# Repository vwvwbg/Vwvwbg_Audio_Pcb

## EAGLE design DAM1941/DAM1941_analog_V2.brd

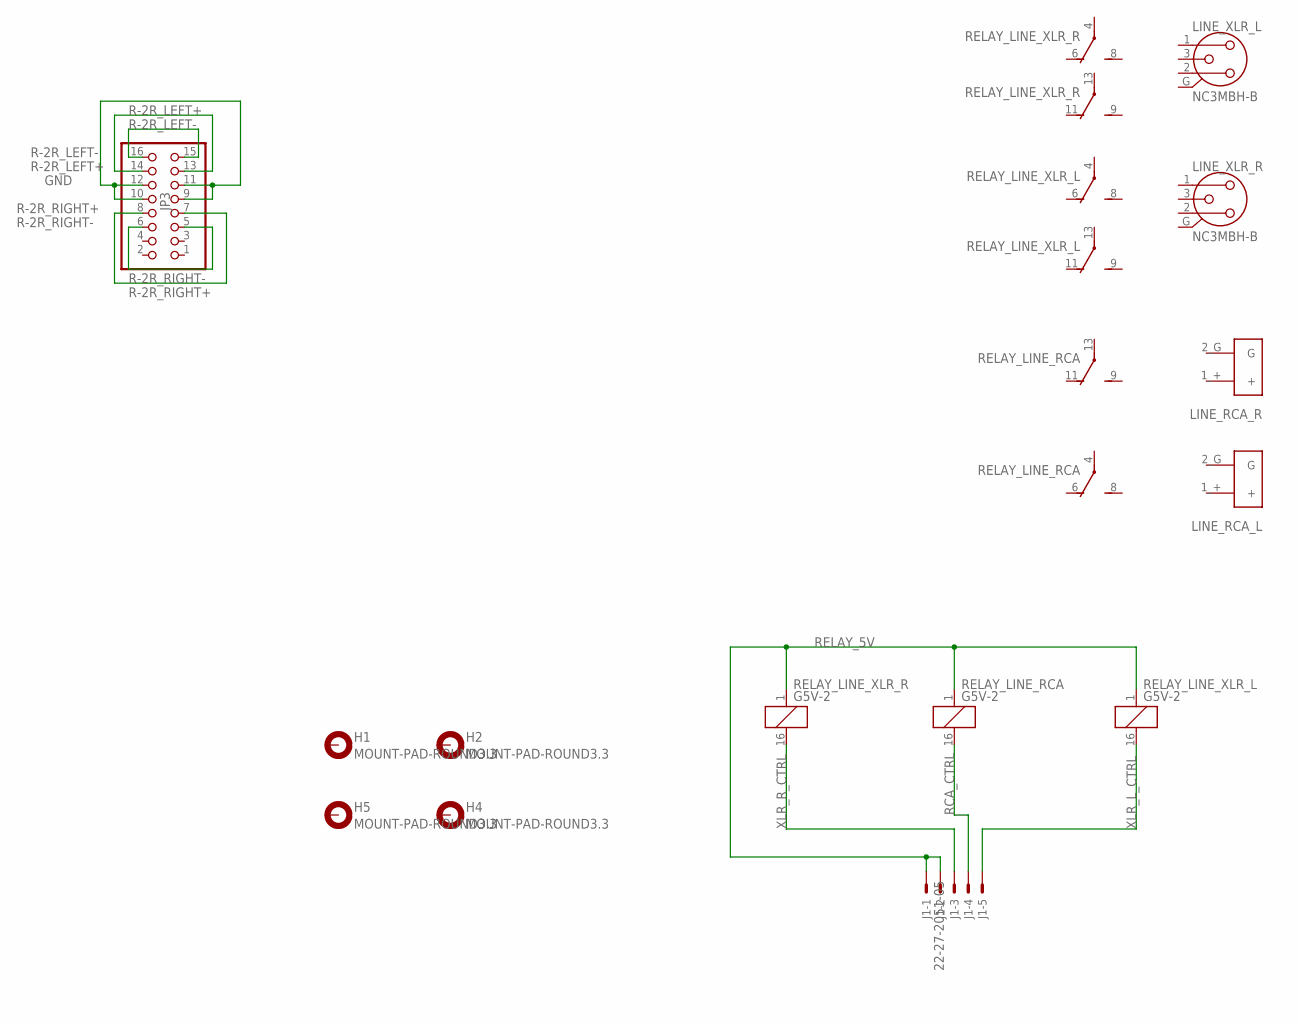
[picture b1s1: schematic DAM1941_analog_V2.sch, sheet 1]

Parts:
H1, H2, H4, H5: MOUNT-PAD-ROUND3.3; 3,3-PAD
J1: 22-27-2051-05; 6410-05
JP3: PINHD-2X8; 2X08
LINE_RCA_L: RCA
LINE_RCA_R: RCA
LINE_XLR_L: NC3MBH-B
LINE_XLR_R: NC3MBH-B
RELAY_LINE_RCA: G5V-2
RELAY_LINE_XLR_L: G5V-2
RELAY_LINE_XLR_R: G5V-2

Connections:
GND: JP3.9, JP3.10, JP3.11, JP3.12; also elsewhere on the board
R-2R_LEFT+: JP3.13, JP3.14
R-2R_LEFT-: JP3.15, JP3.16
R-2R_RIGHT+: JP3.7, JP3.8
R-2R_RIGHT-: JP3.5, JP3.6
RCA_CTRL: J1.4, RELAY_LINE_RCA.16 (2)
RELAY_5V: J1.1, J1.2, RELAY_LINE_RCA.1, RELAY_LINE_XLR_L.1, RELAY_LINE_XLR_R.1
XLR_L_CTRL: J1.5, RELAY_LINE_XLR_L.16 (2)
XLR_R_CTRL: J1.3, RELAY_LINE_XLR_R.16 (2)

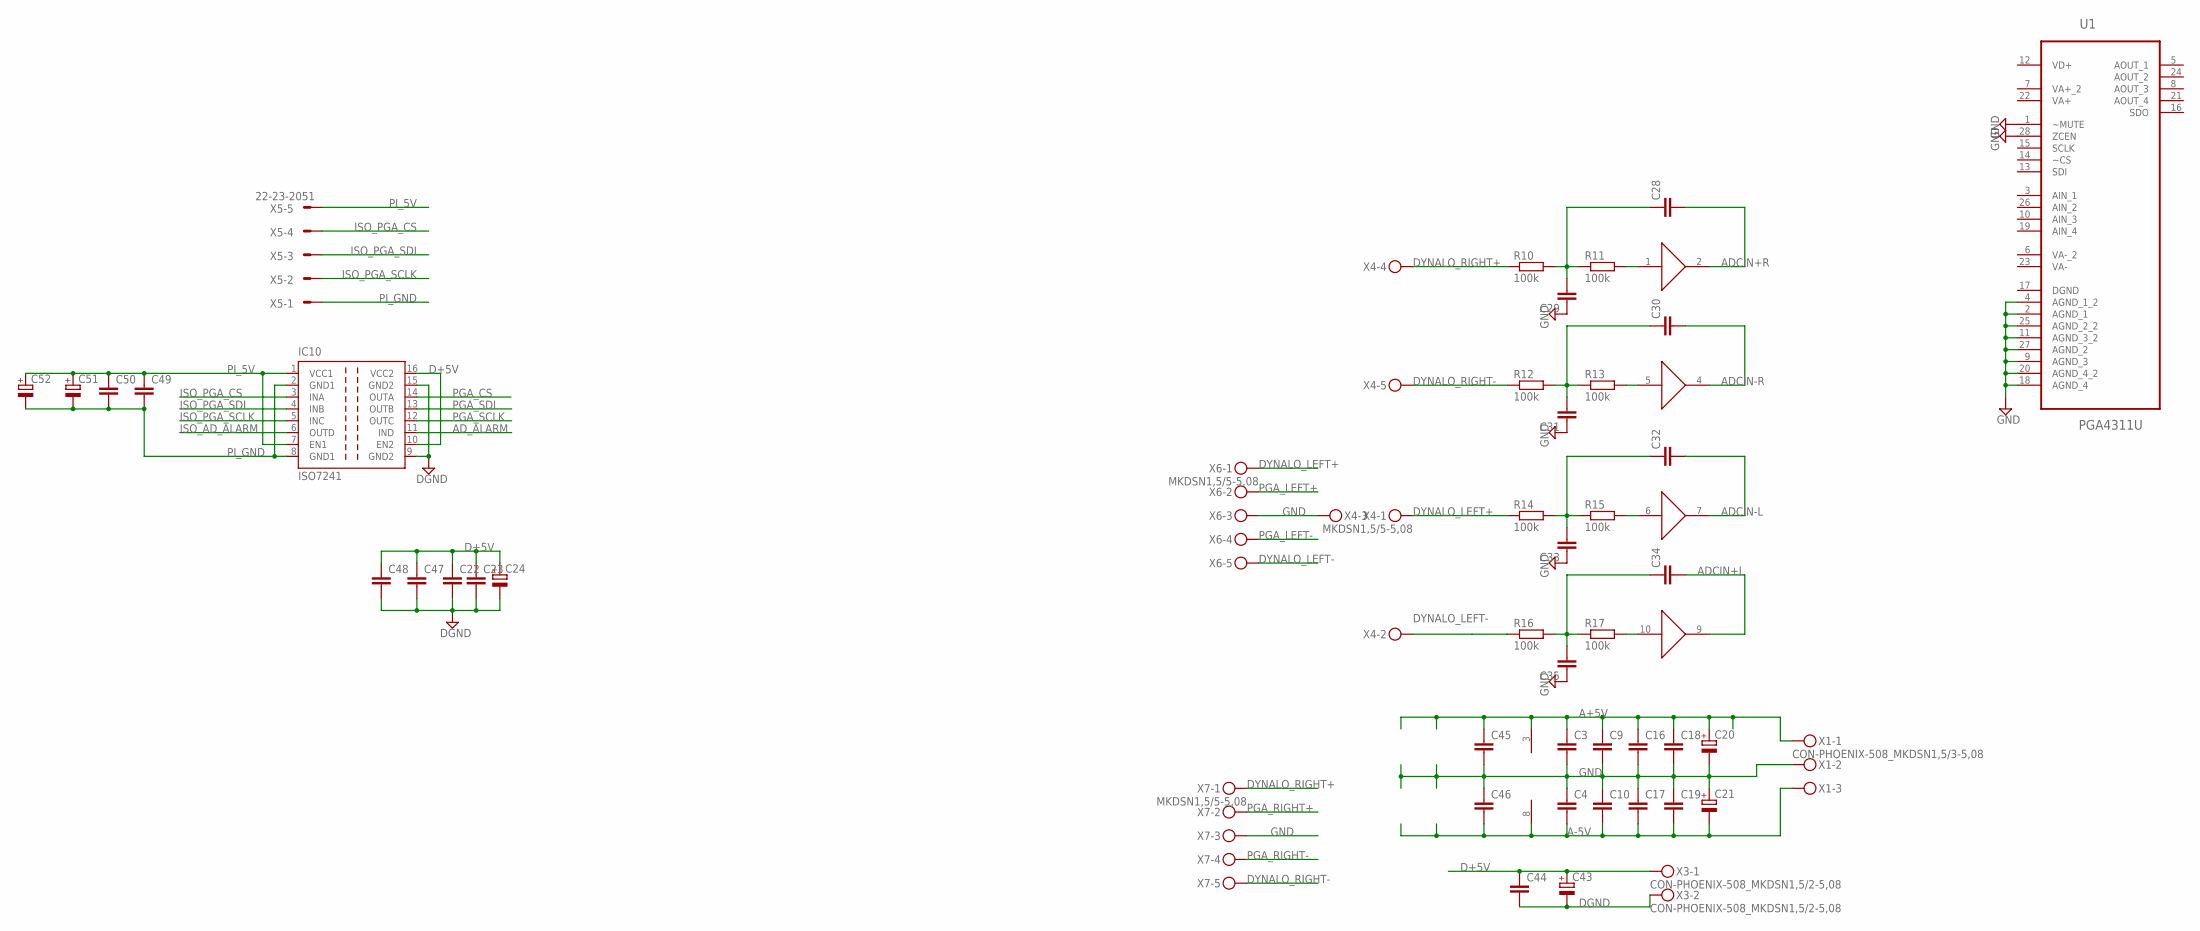
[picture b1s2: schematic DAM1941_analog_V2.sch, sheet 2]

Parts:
C3, C4, C9, C10, C16, C17, C18, C19, C22, C23, C44: C-EU050-050X075; C050-050X075
C20, C21, C24, C43: CPOL-EUE5-10.5; E5-10,5
C28, C29, C30, C31, C32, C33, C34, C35: C-EUC1206; C1206
C45, C46, C47, C48, C49, C50: C-EUC0603K; C0603K
C51, C52: CPOL-EUE5-8.5; E5-8,5
IC10: ISO7241; SO-16DW
R10, R11, R12, R13, R14, R15, R16, R17: 100k; MINI_MELF-0204R
U1: PGA4311U; SOIC127P1030X265-28N
U$3: AD8244; MSOP10
X1: CON-PHOENIX-508_MKDSN1,5/3-5,08
X3: CON-PHOENIX-508_MKDSN1,5/2-5,08
X4, X6, X7: MKDSN1,5/5-5,08
X5: 22-23-2051

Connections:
A+5V: C3.1, C9.1, C16.1, C18.1, C20.+, C45.1, U$3.3 (V+), X1.1; also elsewhere on the board
A-5V: C4.2, C10.2, C17.2, C19.2, C21.-, C46.2, U$3.8 (V-), X1.3
ADCIN+L: C34.2, U$3.9 (OUT); also elsewhere on the board
ADCIN+R: C28.2, U$3.2 (OUT); also elsewhere on the board
ADCIN-L: C32.2, U$3.7 (OUT); also elsewhere on the board
ADCIN-R: C30.2, U$3.4 (OUT); also elsewhere on the board
AD_ALARM: IC10.11 (IND); also elsewhere on the board
D+5V: C22.1, C23.1, C24.+, C43.+, C44.1, C47.1, C48.1, IC10.10 (EN2), IC10.16 (VCC2), X3.1; also elsewhere on the board
DGND: C22.2, C23.2, C24.-, C43.-, C44.2, C47.2, C48.2, IC10.9 (GND2), IC10.15 (GND2), X3.2; also elsewhere on the board
DYNALO_LEFT+: R14.1, X4.1, X6.1
DYNALO_LEFT-: R16.1, X4.2, X6.5
DYNALO_RIGHT+: R10.1, X4.4, X7.1
DYNALO_RIGHT-: R12.1, X4.5, X7.5
GND: C3.2, C4.1, C9.2, C10.1, C16.2, C17.1, C18.2, C19.1, C20.-, C21.+, C29.1, C31.1, C33.1, C35.1, C45.2, C46.1, U1.1 (~MUTE), U1.2 (AGND_1), U1.4 (AGND_1_2), U1.9 (AGND_3), U1.11 (AGND_3_2), U1.18 (AGND_4), U1.20 (AGND_4_2), U1.25 (AGND_2_2), U1.27 (AGND_2), U1.28 (ZCEN), X1.2, X4.3, X6.3, X7.3; also elsewhere on the board
ISO_AD_ALARM: IC10.6 (OUTD); also elsewhere on the board
ISO_PGA_CS: IC10.3 (INA), X5.4
ISO_PGA_SCLK: IC10.5 (INC), X5.2
ISO_PGA_SDI: IC10.4 (INB), X5.3
unnamed: C28.1, C29.2, R10.2, R11.1
unnamed: R11.2, U$3.1 (IN)
unnamed: C30.1, C31.2, R12.2, R13.1
unnamed: R13.2, U$3.5 (IN)
unnamed: C32.1, C33.2, R14.2, R15.1
unnamed: R15.2, U$3.6 (IN)
unnamed: C34.1, C35.2, R16.2, R17.1
unnamed: R17.2, U$3.10 (IN)
PGA_CS: IC10.14 (OUTA)
PGA_LEFT+: X6.2
PGA_LEFT-: X6.4
PGA_RIGHT+: X7.2
PGA_RIGHT-: X7.4
PGA_SCLK: IC10.12 (OUTC)
PGA_SDI: IC10.13 (OUTB)
PI_5V: C49.1, C50.1, C51.+, C52.+, IC10.1 (VCC1), IC10.7 (EN1), X5.5; also elsewhere on the board
PI_GND: C49.2, C50.2, C51.-, C52.-, IC10.2 (GND1), IC10.8 (GND1), X5.1; also elsewhere on the board
VA+: U1.22 (VA+)
VA+_2: U1.7 (VA+_2)
VA-: U1.23 (VA-)
VA-_2: U1.6 (VA-_2)
VD+: U1.12 (VD+)

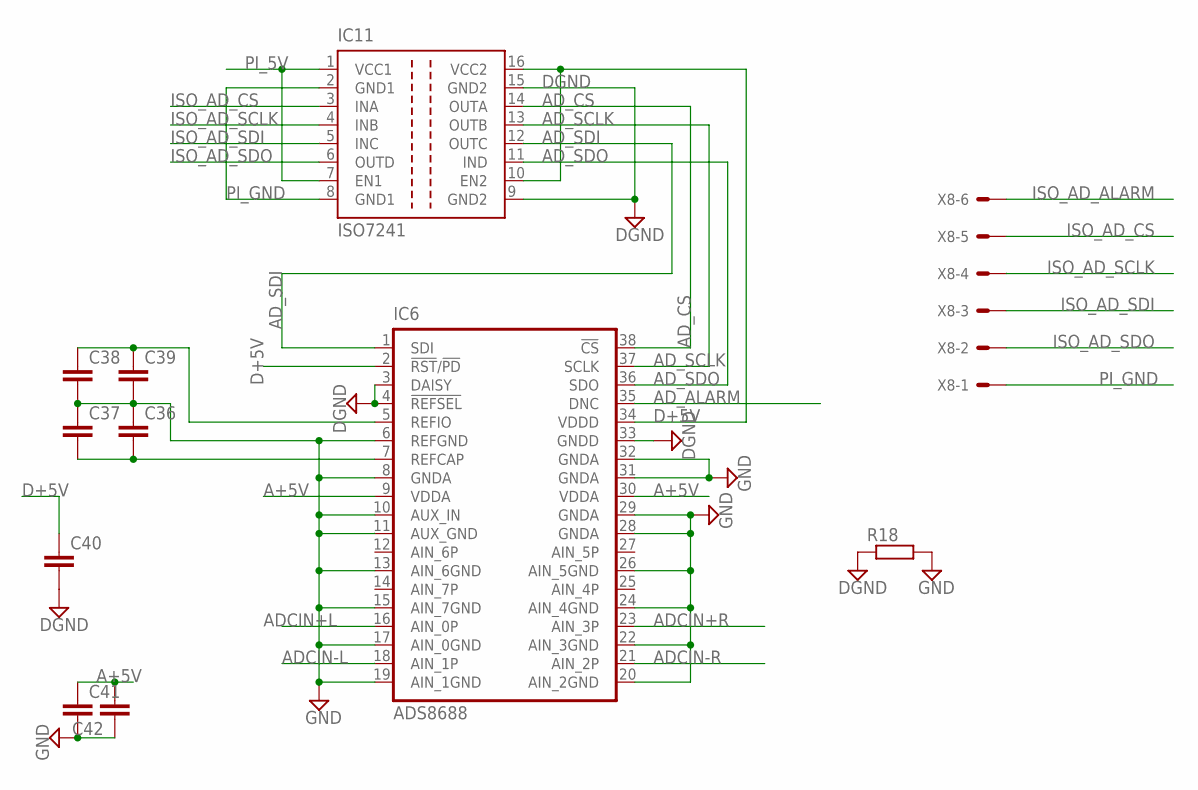
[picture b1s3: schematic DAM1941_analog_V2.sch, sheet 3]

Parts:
C36, C39, C40, C41, C42: C-EUC0603K; C0603K
C37, C38: C-EU050-035X075; C050-035X075
IC6: ADS8688; DBT_R-PDSO-G38
IC11: ISO7241; SO-16DW
R18: R-EU_MELF0204R; MINI_MELF-0204R
X8: 22-23-2061

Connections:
A+5V: C41.1, C42.2, IC6.9 (VDDA), IC6.30 (VDDA); also elsewhere on the board
ADCIN+L: IC6.16 (AIN_0P); also elsewhere on the board
ADCIN+R: IC6.23 (AIN_3P); also elsewhere on the board
ADCIN-L: IC6.18 (AIN_1P); also elsewhere on the board
ADCIN-R: IC6.21 (AIN_2P); also elsewhere on the board
AD_ALARM: IC6.35 (DNC); also elsewhere on the board
AD_CS: IC6.38 (!CS), IC11.14 (OUTA)
AD_SCLK: IC6.37 (SCLK), IC11.13 (OUTB)
AD_SDI: IC6.1 (SDI), IC11.12 (OUTC)
AD_SDO: IC6.36 (SDO), IC11.11 (IND)
D+5V: C40.1, IC6.2 (!RST!/!PD), IC6.34 (VDDD), IC11.10 (EN2), IC11.16 (VCC2); also elsewhere on the board
DGND: C40.2, IC6.3 (DAISY), IC6.4 (!REFSEL), IC6.33 (GNDD), IC11.9 (GND2), IC11.15 (GND2), R18.1; also elsewhere on the board
GND: C36.1, C37.1, C38.2, C39.2, C41.2, C42.1, IC6.6 (REFGND), IC6.8 (GNDA), IC6.10 (AUX_IN), IC6.11 (AUX_GND), IC6.13 (AIN_6GND), IC6.15 (AIN_7GND), IC6.17 (AIN_0GND), IC6.19 (AIN_1GND), IC6.20 (AIN_2GND), IC6.22 (AIN_3GND), IC6.24 (AIN_4GND), IC6.26 (AIN_5GND), IC6.28 (GNDA), IC6.29 (GNDA), IC6.31 (GNDA), IC6.32 (GNDA), R18.2; also elsewhere on the board
ISO_AD_ALARM: X8.6; also elsewhere on the board
ISO_AD_CS: IC11.3 (INA), X8.5
ISO_AD_SCLK: IC11.4 (INB), X8.4
ISO_AD_SDI: IC11.5 (INC), X8.3
ISO_AD_SDO: IC11.6 (OUTD), X8.2
unnamed: C36.2, C37.2, IC6.7 (REFCAP)
unnamed: C38.1, C39.1, IC6.5 (REFIO)
PI_5V: IC11.1 (VCC1), IC11.7 (EN1); also elsewhere on the board
PI_GND: IC11.2 (GND1), IC11.8 (GND1), X8.1; also elsewhere on the board

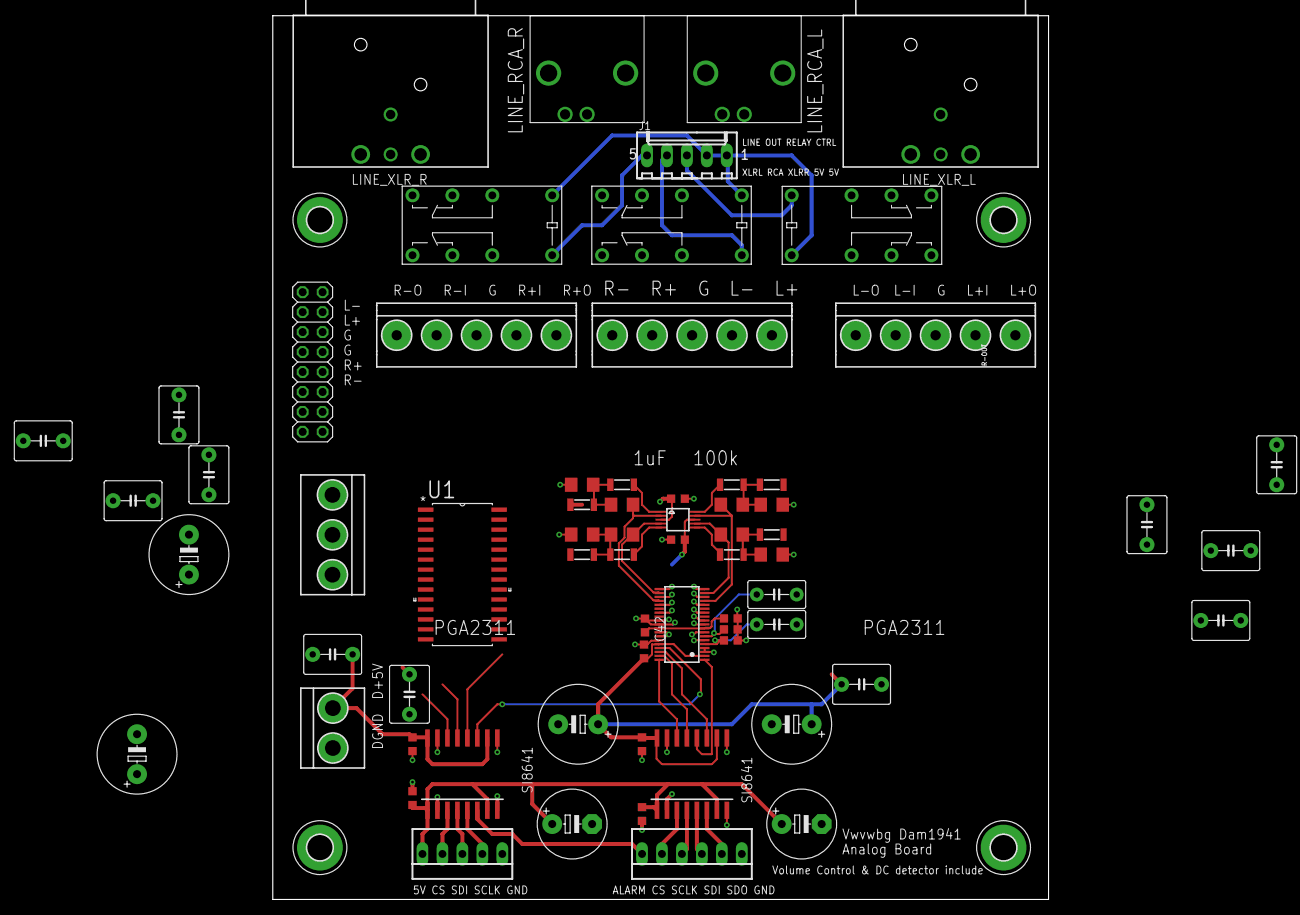
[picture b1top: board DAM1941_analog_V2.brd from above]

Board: 2 copper layers, 98.7 x 112.5 mm, 72 parts (1 on the bottom side), 46 nets.

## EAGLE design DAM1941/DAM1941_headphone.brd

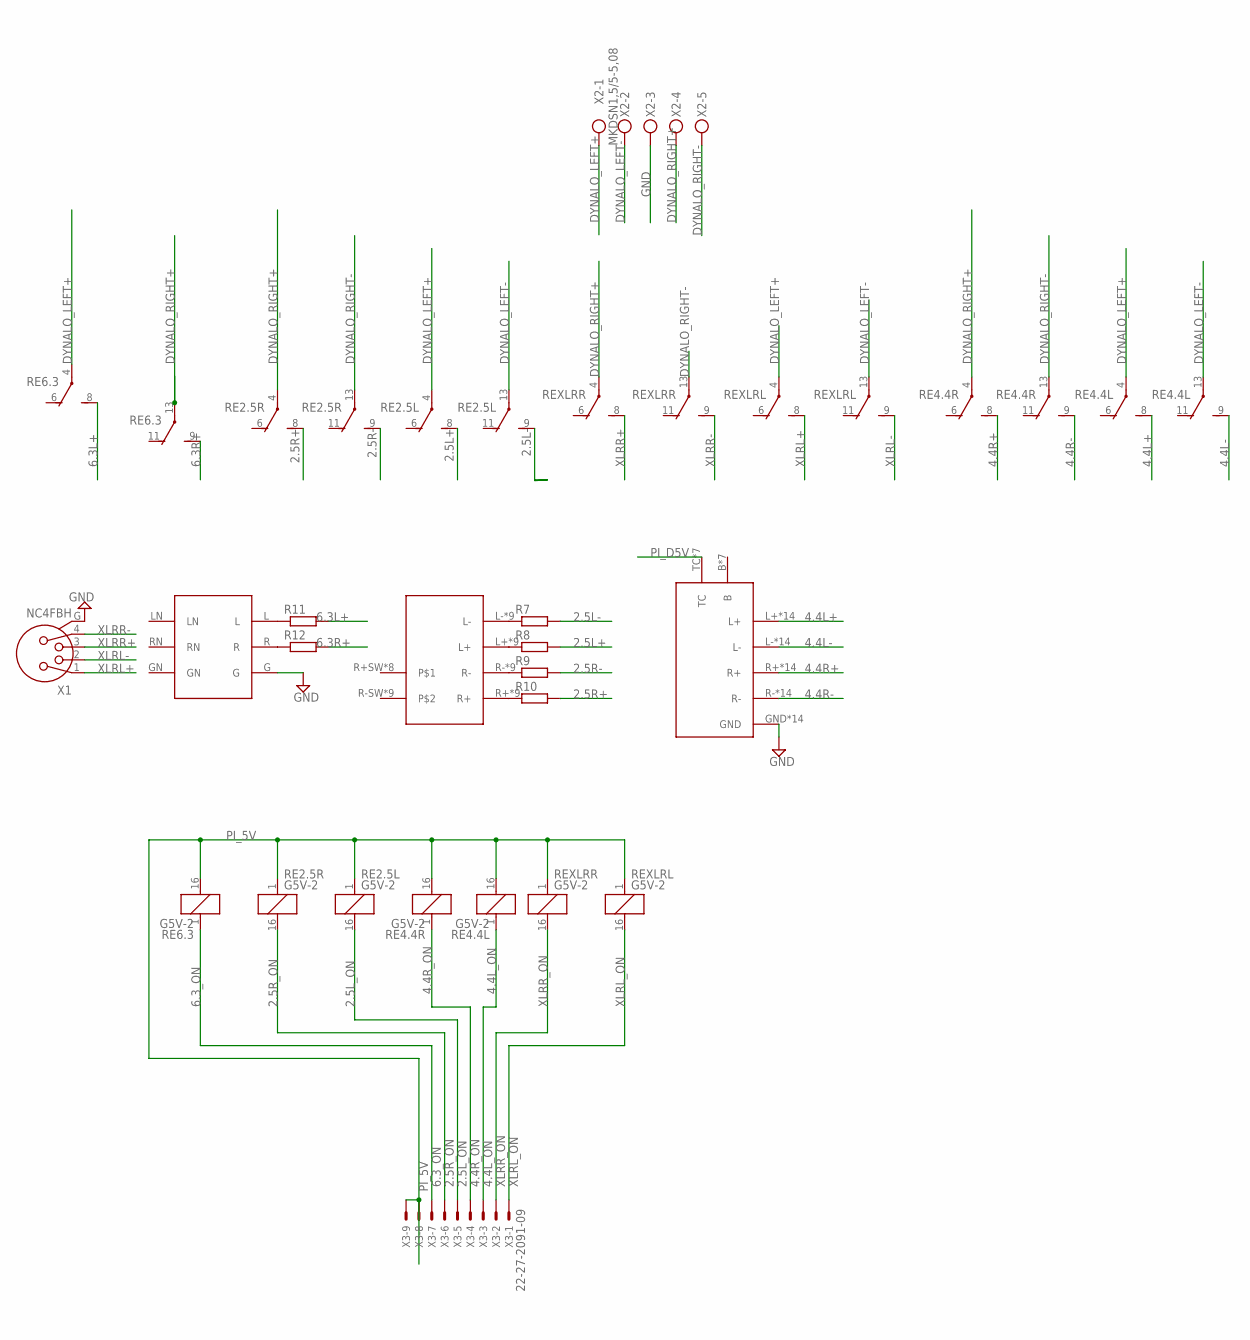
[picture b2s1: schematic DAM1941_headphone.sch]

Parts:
R7, R8, R9, R10, R11, R12: R-EU_MELF0204R; MINI_MELF-0204R
RE2.5L, RE2.5R, RE4.4L, RE4.4R, RE6.3: G5V-2
REXLRL: G5V-2
REXLRR: G5V-2
U$1: PANTACON_JACK; PATNACON_JACK
U$2: CUI2.5MM
U$3: NMJ6HCD3; NMJ6HCD3-AU
X1: NC4FBH
X2: MKDSN1,5/5-5,08
X3: 22-27-2091-09; 6410-09

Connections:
2.5L+: R8.2, RE2.5L.8 (S)
2.5L-: R7.2, RE2.5L.9 (S)
2.5L_ON: RE2.5L.16 (2), X3.5
2.5R+: R10.2, RE2.5R.8 (S)
2.5R-: R9.2, RE2.5R.9 (S)
2.5R_ON: RE2.5R.16 (2), X3.6
4.4L+: RE4.4L.8 (S), U$1.L+, U$1.L+1 (L+), U$1.L+2 (L+), U$1.L+3 (L+), U$1.L+4 (L+), U$1.L+5 (L+), U$1.L+6 (L+), U$1.L+7 (L+), U$1.L+8 (L+), U$1.L+9 (L+), U$1.L+10 (L+), U$1.L+11 (L+), U$1.L+12 (L+), U$1.L+13 (L+)
4.4L-: RE4.4L.9 (S), U$1.L-, U$1.L-1 (L-), U$1.L-2 (L-), U$1.L-3 (L-), U$1.L-4 (L-), U$1.L-5 (L-), U$1.L-6 (L-), U$1.L-7 (L-), U$1.L-8 (L-), U$1.L-9 (L-), U$1.L-10 (L-), U$1.L-11 (L-), U$1.L-12 (L-), U$1.L-13 (L-)
4.4L_ON: RE4.4L.1, X3.3
4.4R+: RE4.4R.8 (S), U$1.R+, U$1.R+1 (R+), U$1.R+2 (R+), U$1.R+3 (R+), U$1.R+4 (R+), U$1.R+5 (R+), U$1.R+6 (R+), U$1.R+7 (R+), U$1.R+8 (R+), U$1.R+9 (R+), U$1.R+10 (R+), U$1.R+11 (R+), U$1.R+12 (R+), U$1.R+13 (R+)
4.4R-: RE4.4R.9 (S), U$1.R-, U$1.R-1 (R-), U$1.R-2 (R-), U$1.R-3 (R-), U$1.R-4 (R-), U$1.R-5 (R-), U$1.R-6 (R-), U$1.R-7 (R-), U$1.R-8 (R-), U$1.R-9 (R-), U$1.R-10 (R-), U$1.R-11 (R-), U$1.R-12 (R-), U$1.R-13 (R-)
4.4R_ON: RE4.4R.1, X3.4
6.3L+: R11.2, RE6.3.8 (S)
6.3R+: R12.2, RE6.3.9 (S)
6.3_ON: RE6.3.1, X3.7
DYNALO_LEFT+: RE2.5L.4, RE4.4L.4, RE6.3.4, REXLRL.4, X2.1
DYNALO_LEFT-: RE2.5L.13, RE4.4L.13, REXLRL.13, X2.2
DYNALO_RIGHT+: RE2.5R.4, RE4.4R.4, RE6.3.13, REXLRR.4, X2.4
DYNALO_RIGHT-: RE2.5R.13, RE4.4R.13, REXLRR.13, X2.5
GND: U$1.GND, U$1.GND1 (GND), U$1.GND2 (GND), U$1.GND3 (GND), U$1.GND4 (GND), U$1.GND5 (GND), U$1.GND6 (GND), U$1.GND7 (GND), U$1.GND8 (GND), U$1.GND9 (GND), U$1.GND10 (GND), U$1.GND11 (GND), U$1.GND12 (GND), U$1.GND13 (GND), U$3.G, X1.G, X2.3
unnamed: R7.1, U$2.L-, U$2.L-1 (L-), U$2.L-2 (L-), U$2.L-3 (L-), U$2.L-4 (L-), U$2.L-5 (L-), U$2.L-6 (L-), U$2.L-7 (L-), U$2.L-8 (L-)
unnamed: R8.1, U$2.L+, U$2.L+1 (L+), U$2.L+2 (L+), U$2.L+3 (L+), U$2.L+4 (L+), U$2.L+5 (L+), U$2.L+6 (L+), U$2.L+7 (L+), U$2.L+8 (L+)
unnamed: R9.1, U$2.R-, U$2.R-1 (R-), U$2.R-2 (R-), U$2.R-3 (R-), U$2.R-4 (R-), U$2.R-5 (R-), U$2.R-6 (R-), U$2.R-7 (R-), U$2.R-8 (R-)
unnamed: R10.1, U$2.R+, U$2.R+1 (R+), U$2.R+2 (R+), U$2.R+3 (R+), U$2.R+4 (R+), U$2.R+5 (R+), U$2.R+6 (R+), U$2.R+7 (R+), U$2.R+8 (R+)
unnamed: R11.1, U$3.L
unnamed: R12.1, U$3.R
PI_5V: RE2.5L.1, RE2.5R.1, RE4.4L.16 (2), RE4.4R.16 (2), RE6.3.16 (2), REXLRL.1, REXLRR.1, X3.8, X3.9
PI_D5V: U$1.TC, U$1.TC1 (TC), U$1.TC2 (TC), U$1.TC3 (TC), U$1.TC4 (TC), U$1.TC5 (TC), U$1.TC6 (TC)
XLRL+: REXLRL.8 (S), X1.1
XLRL-: REXLRL.9 (S), X1.2
XLRL_ON: REXLRL.16 (2), X3.1
XLRR+: REXLRR.8 (S), X1.3
XLRR-: REXLRR.9 (S), X1.4
XLRR_ON: REXLRR.16 (2), X3.2

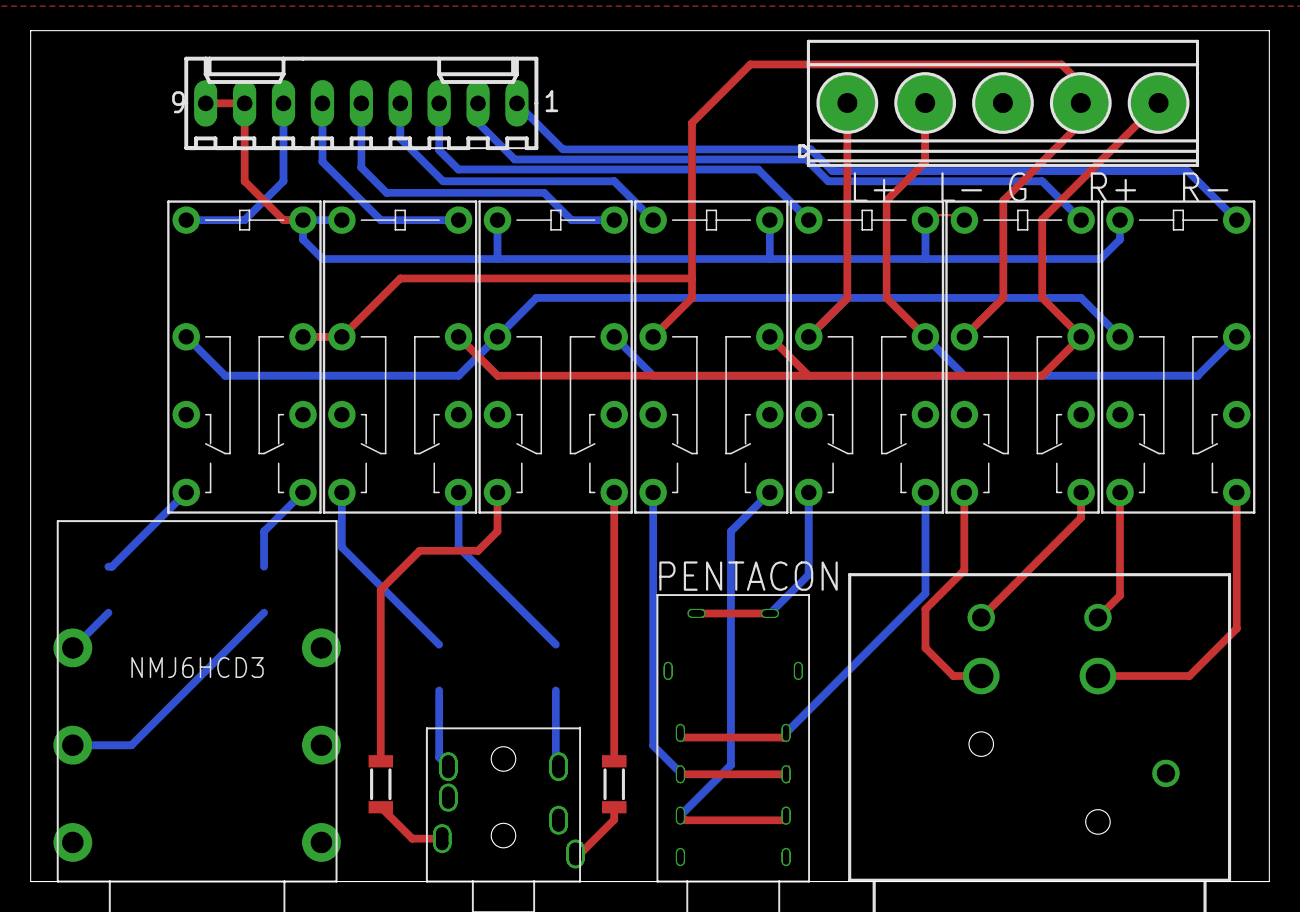
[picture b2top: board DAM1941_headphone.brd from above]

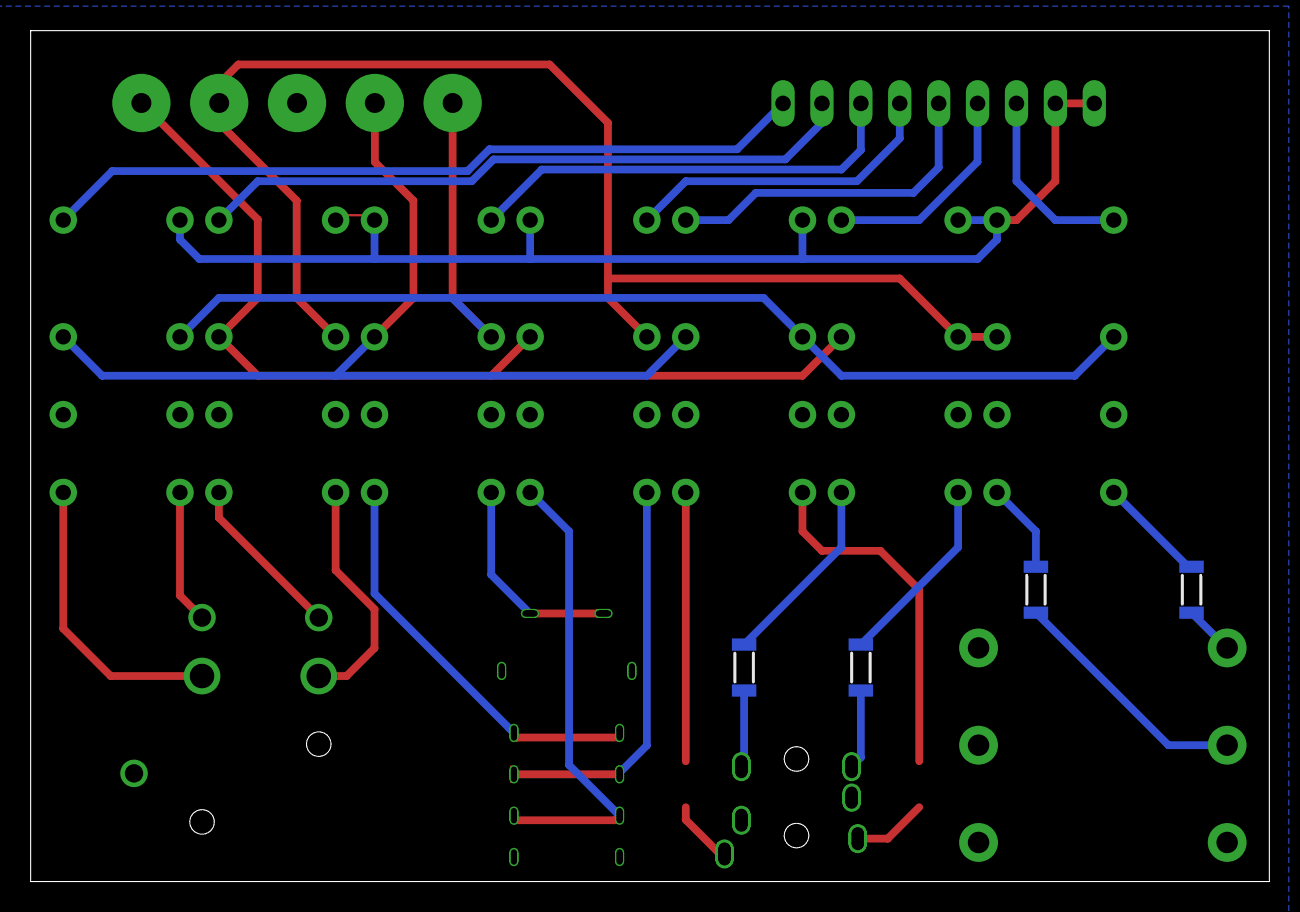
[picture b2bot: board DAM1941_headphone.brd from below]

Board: 2 copper layers, 80.9 x 55.5 mm, 19 parts (4 on the bottom side), 34 nets.

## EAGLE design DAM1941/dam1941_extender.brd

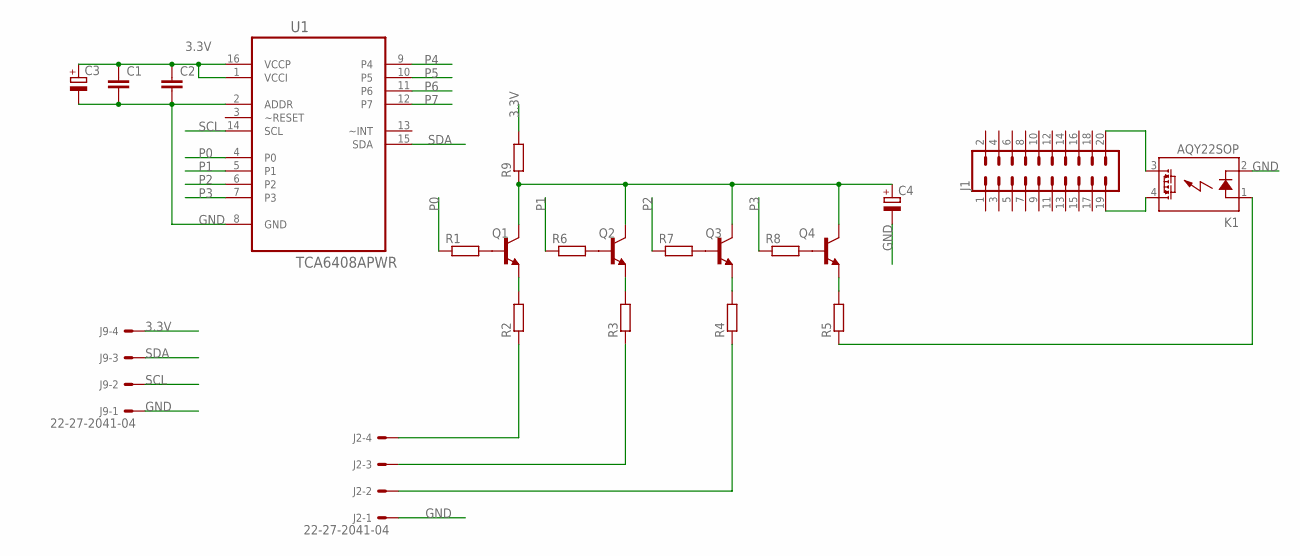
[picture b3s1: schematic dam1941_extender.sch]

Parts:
C1, C2: C-EUC0805; C0805
C3, C4: CPOL-EUE2.5-6; E2,5-6
J1: CONN_10X22X10_LOCK; 2X10_LOCK
J2, J9: 22-27-2041-04; 6410-04
K1: AQY22SOP; SOP04
Q1, Q2, Q3, Q4: TRANSISTOR_BC850-NPN-SOT23-BEC; TRANSISTOR_SOT23-BEC
R1, R2, R3, R4, R5, R6, R7, R8, R9: R-EU_MELF0204W; MINI_MELF-0204W
U1: TCA6408APWR; SOP65P640X120-16N

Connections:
3.3V: C1.1, C2.1, C3.+, J9.4, R9.2, U1.1 (VCCI), U1.16 (VCCP)
GND: C1.2, C2.2, C3.-, C4.-, J2.1, J9.1, K1.2 (K), U1.2 (ADDR), U1.8 (GND)
unnamed: J1.20, K1.3 (DS2)
unnamed: J1.19, K1.4 (DS1)
unnamed: C4.+, Q1.C, Q2.C, Q3.C, Q4.C, R9.1
unnamed: Q1.E, R2.2
unnamed: Q3.B, R7.2
unnamed: Q4.B, R8.2
unnamed: Q2.B, R6.2
unnamed: Q1.B, R1.2
unnamed: Q2.E, R3.2
unnamed: Q3.E, R4.2
unnamed: Q4.E, R5.2
unnamed: J2.4, R2.1
unnamed: K1.1 (A), R5.1
unnamed: J2.3, R3.1
unnamed: J2.2, R4.1
P0: R1.1, U1.4 (P0)
P1: R6.1, U1.5 (P1)
P2: R7.1, U1.6 (P2)
P3: R8.1, U1.7 (P3)
P4: U1.9 (P4)
P5: U1.10 (P5)
P6: U1.11 (P6)
P7: U1.12 (P7)
SCL: J9.2, U1.14 (SCL)
SDA: J9.3, U1.15 (SDA)

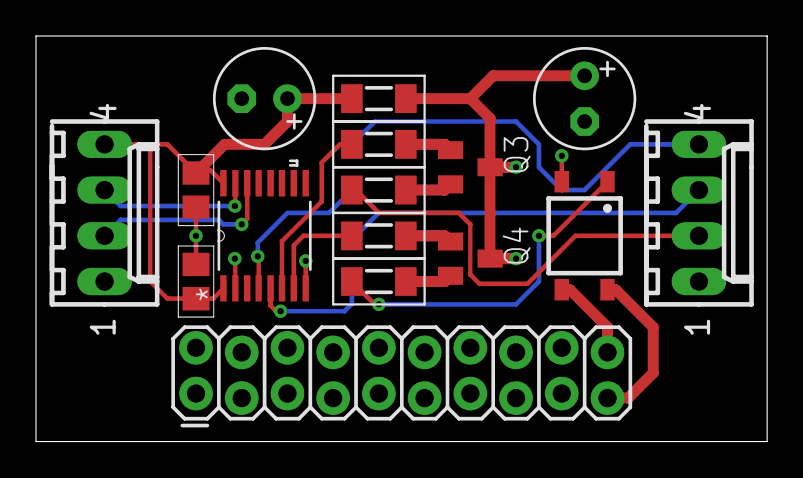
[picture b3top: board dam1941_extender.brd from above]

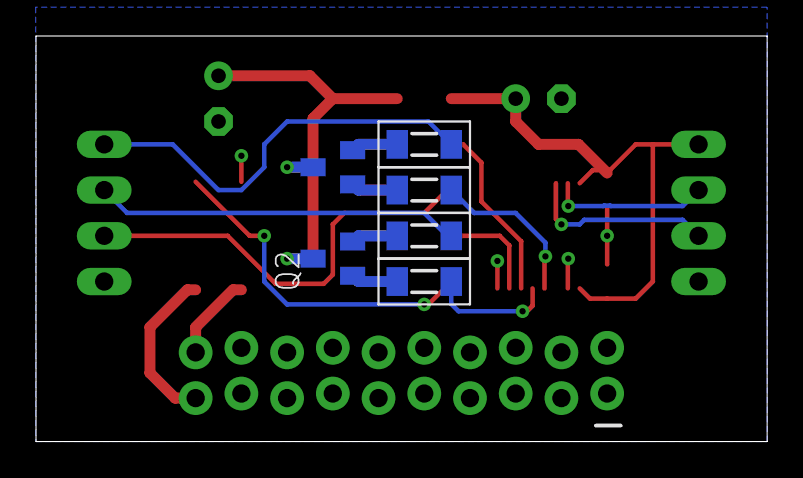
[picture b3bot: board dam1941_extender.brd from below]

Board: 2 copper layers, 40.6 x 22.5 mm, 22 parts (6 on the bottom side), 23 nets.

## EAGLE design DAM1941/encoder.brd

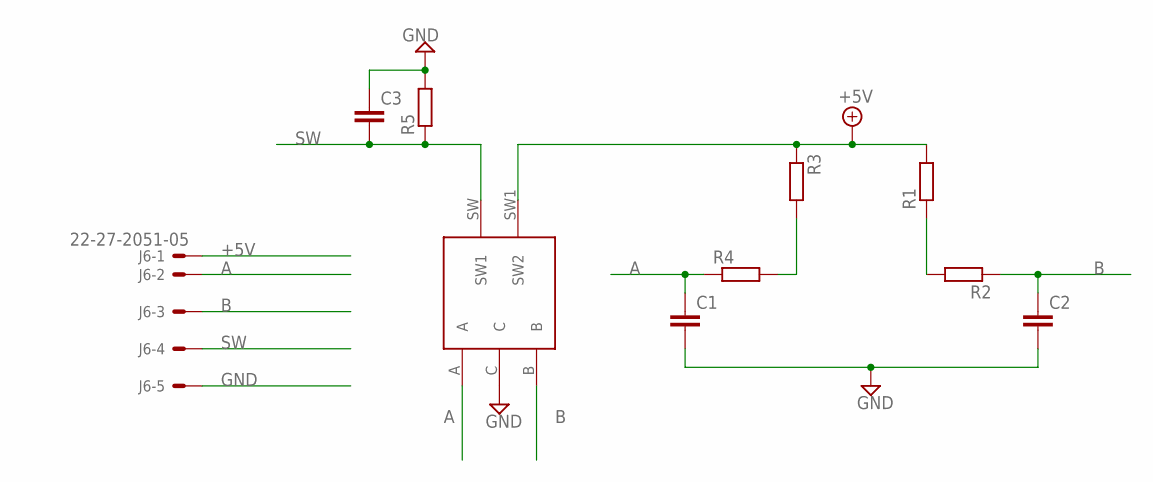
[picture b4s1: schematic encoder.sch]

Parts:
C1, C2, C3: C-EUC0805; C0805
J6: 22-27-2051-05; 6410-05
R1, R2, R3, R4, R5: R-EU_MELF0204W; MINI_MELF-0204W
U$1: BOURNS_ROTARY

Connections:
+5V: J6.1, R1.2, R3.1, U$1.SW1 (SW2)
A: C1.1, J6.2, R4.1, U$1.A
B: C2.1, J6.3, R2.1, U$1.B
GND: C1.2, C2.2, C3.1, J6.5, R5.2, U$1.C
unnamed: R1.1, R2.2
unnamed: R3.2, R4.2
SW: C3.2, J6.4, R5.1, U$1.SW (SW1)

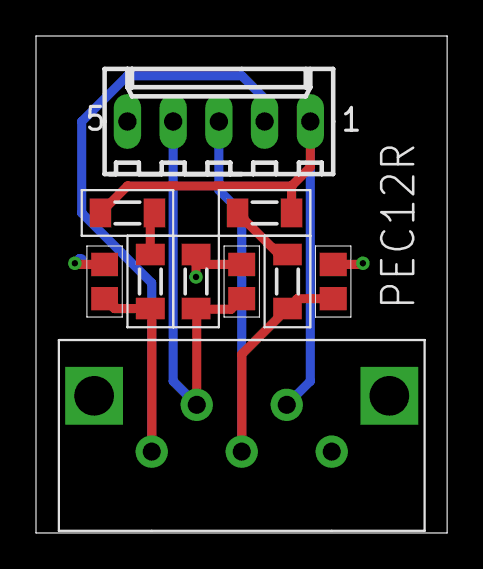
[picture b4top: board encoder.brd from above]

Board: 2 copper layers, 22.8 x 27.6 mm, 10 parts (0 on the bottom side), 7 nets.

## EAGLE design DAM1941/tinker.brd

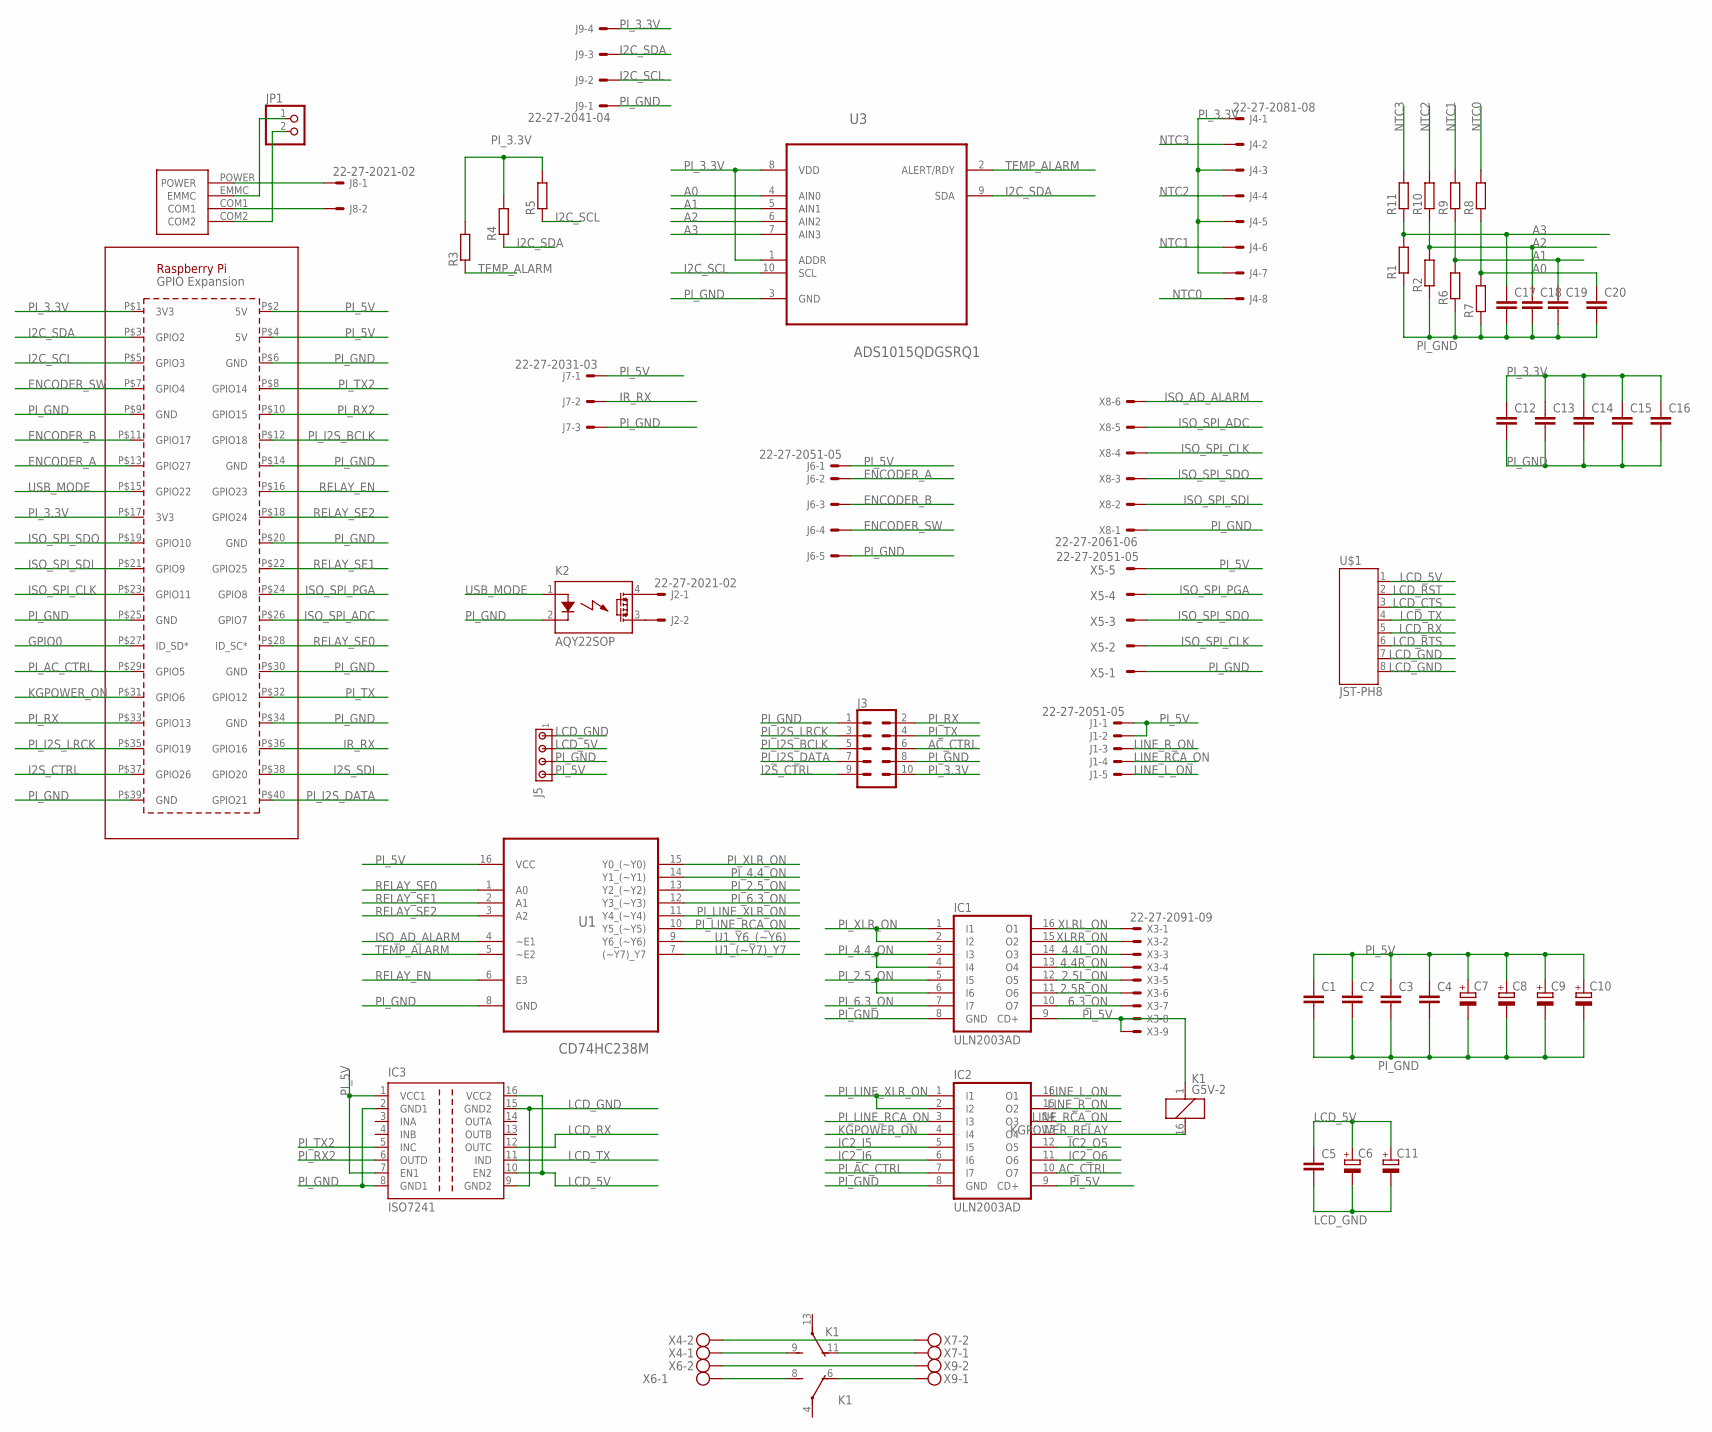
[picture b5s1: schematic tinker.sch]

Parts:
C1, C2, C3, C4, C5, C12, C13, C14, C15, C16, C17, C18, C19, C20: C-EUC0603; C0603
C6, C11: CPOL-EUSP-CAP-CX; SP-CAP-CX
C7, C8, C9, C10: CPOL-EUE5-10.5; E5-10,5
IC1, IC2: ULN2003AD; SO16
IC3: ISO7241; SO-16DW
J1, J6: 22-27-2051-05; 6410-05
J2, J8: 22-27-2021-02; 6410-02
J3: CONN_05X2SHD_LOCK; 2X5-SHROUDED_LOCK
J4: 22-27-2081-08; 6410-08
J5: MTA04-156; 1X4MTA
J7: 22-27-2031-03; 6410-03
J9: 22-27-2041-04; 6410-04
JP1: PINHD-1X2; 1X02
K1: G5V-2
K2: AQY22SOP; SOP04
PCB1: RPI3
R1, R2, R3, R4, R5, R6, R7, R8, R9, R10, R11: R-EU_MELF0204W; MINI_MELF-0204W
U1: CD74HC238M; SOIC127P600X175-16N
U3: ADS1015QDGSRQ1; SOP50P490X110-10N
U$1: JST-PH8
X3: 22-27-2091-09; 6410-09
X4, X6, X7, X9: CON-PHOENIX-508_MKDSN1,5/2-5,08
X5: 22-27-2051-05; 6410-05
X8: 22-27-2061-06; 6410-06

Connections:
2.5L_ON: IC1.12 (O5), X3.5
2.5R_ON: IC1.11 (O6), X3.6
4.4L_ON: IC1.14 (O3), X3.3
4.4R_ON: IC1.13 (O4), X3.4
6.3_ON: IC1.10 (O7), X3.7
A0: C20.1, R7.2, R8.1, U3.4 (AIN0)
A1: C19.1, R6.2, R9.1, U3.5 (AIN1)
A2: C18.1, R2.2, R10.1, U3.6 (AIN2)
A3: C17.1, R1.2, R11.1, U3.7 (AIN3)
AC_CTRL: IC2.10 (O7), J3.6
ENCODER_A: J6.2, PCB1.P$13 (GPIO27)
ENCODER_B: J6.3, PCB1.P$11 (GPIO17)
ENCODER_SW: J6.4, PCB1.P$7 (GPIO4)
GPIO0: PCB1.P$27 (ID_SD*)
I2C_SCL: J9.2, PCB1.P$5 (GPIO3), R5.1, U3.10 (SCL)
I2C_SDA: J9.3, PCB1.P$3 (GPIO2), R4.1, U3.9 (SDA)
I2S_CTRL: J3.9, PCB1.P$37 (GPIO26)
I2S_SDI: PCB1.P$38 (GPIO20)
IC2_I5: IC2.5 (I5)
IC2_I6: IC2.6 (I6)
IC2_O5: IC2.12 (O5)
IC2_O6: IC2.11 (O6)
IR_RX: J7.2, PCB1.P$36 (GPIO16)
ISO_AD_ALARM: U1.4 (~E1), X8.6
ISO_SPI_ADC: PCB1.P$26 (GPIO7), X8.5
ISO_SPI_CLK: PCB1.P$23 (GPIO11), X5.2, X8.4
ISO_SPI_PGA: PCB1.P$24 (GPIO8), X5.4
ISO_SPI_SDI: PCB1.P$21 (GPIO9), X8.2
ISO_SPI_SDO: PCB1.P$19 (GPIO10), X5.3, X8.3
KGPOWER_ON: IC2.4 (I4), PCB1.P$31 (GPIO6)
KGPOWER_RELAY: IC2.13 (O4), K1.16 (2)
LCD_5V: C5.1, C6.+, C11.+, IC3.10 (EN2), IC3.16 (VCC2), J5.2, U$1.1
LCD_CTS: U$1.3
LCD_GND: C5.2, C6.-, C11.-, IC3.9 (GND2), IC3.15 (GND2), J5.1, U$1.7, U$1.8
LCD_RST: U$1.2
LCD_RTS: U$1.6
LCD_RX: IC3.12 (OUTC), U$1.5
LCD_TX: IC3.11 (IND), U$1.4
LINE_L_ON: IC2.16 (O1), J1.5
LINE_RCA_ON: IC2.14 (O3), J1.4
LINE_R_ON: IC2.15 (O2), J1.3
unnamed: K1.8 (S), X6.1
unnamed: K1.6 (O), X9.1
unnamed: K1.11 (O), X7.1
unnamed: K1.9 (S), X4.1
unnamed: X6.2, X9.2
unnamed: X4.2, X7.2
unnamed: J2.1, K2.4 (DS1)
unnamed: J2.2, K2.3 (DS2)
unnamed: J8.1, PCB1.POWER
unnamed: J8.2, PCB1.COM1
unnamed: JP1.1, PCB1.EMMC
unnamed: JP1.2, PCB1.COM2
NTC0: J4.8, R8.2
NTC1: J4.6, R9.2
NTC2: J4.4, R10.2
NTC3: J4.2, R11.2
PI_2.5_ON: IC1.5 (I5), IC1.6 (I6), U1.13 (Y2_(~Y2))
PI_3.3V: C12.1, C13.1, C14.1, C15.1, C16.1, J3.10, J4.1, J4.3, J4.5, J4.7, J9.4, PCB1.P$1 (3V3), PCB1.P$17 (3V3), R3.2, R4.2, R5.2, U3.1 (ADDR), U3.8 (VDD)
PI_4.4_ON: IC1.3 (I3), IC1.4 (I4), U1.14 (Y1_(~Y1))
PI_5V: C1.1, C2.1, C3.1, C4.1, C7.+, C8.+, C9.+, C10.+, IC1.9 (CD+), IC2.9 (CD+), IC3.1 (VCC1), IC3.7 (EN1), J1.1, J1.2, J5.4, J6.1, J7.1, K1.1, PCB1.P$2 (5V), PCB1.P$4 (5V), U1.16 (VCC), X3.8, X3.9, X5.5
PI_6.3_ON: IC1.7 (I7), U1.12 (Y3_(~Y3))
PI_AC_CTRL: IC2.7 (I7), PCB1.P$29 (GPIO5)
PI_GND: C1.2, C2.2, C3.2, C4.2, C7.-, C8.-, C9.-, C10.-, C12.2, C13.2, C14.2, C15.2, C16.2, C17.2, C18.2, C19.2, C20.2, IC1.8 (GND), IC2.8 (GND), IC3.2 (GND1), IC3.8 (GND1), J3.1, J3.8, J5.3, J6.5, J7.3, J9.1, K2.2 (K), PCB1.P$6 (GND), PCB1.P$9 (GND), PCB1.P$14 (GND), PCB1.P$20 (GND), PCB1.P$25 (GND), PCB1.P$30 (GND), PCB1.P$34 (GND), PCB1.P$39 (GND), R1.1, R2.1, R6.1, R7.1, U1.8 (GND), U3.3 (GND), X5.1, X8.1
PI_I2S_BCLK: J3.5, PCB1.P$12 (GPIO18)
PI_I2S_DATA: J3.7, PCB1.P$40 (GPIO21)
PI_I2S_LRCK: J3.3, PCB1.P$35 (GPIO19)
PI_LINE_RCA_ON: IC2.3 (I3), U1.10 (Y5_(~Y5))
PI_LINE_XLR_ON: IC2.1 (I1), IC2.2 (I2), U1.11 (Y4_(~Y4))
PI_RX: J3.2, PCB1.P$33 (GPIO13)
PI_RX2: IC3.6 (OUTD), PCB1.P$10 (GPIO15)
PI_TX: J3.4, PCB1.P$32 (GPIO12)
PI_TX2: IC3.5 (INC), PCB1.P$8 (GPIO14)
PI_XLR_ON: IC1.1 (I1), IC1.2 (I2), U1.15 (Y0_(~Y0))
RELAY_EN: PCB1.P$16 (GPIO23), U1.6 (E3)
RELAY_SE0: PCB1.P$28 (ID_SC*), U1.1 (A0)
RELAY_SE1: PCB1.P$22 (GPIO25), U1.2 (A1)
RELAY_SE2: PCB1.P$18 (GPIO24), U1.3 (A2)
TEMP_ALARM: R3.1, U1.5 (~E2), U3.2 (ALERT/RDY)
U1_(~Y7)_Y7: U1.7 ((~Y7)_Y7)
U1_Y6_(~Y6): U1.9 (Y6_(~Y6))
USB_MODE: K2.1 (A), PCB1.P$15 (GPIO22)
XLRL_ON: IC1.16 (O1), X3.1
XLRR_ON: IC1.15 (O2), X3.2

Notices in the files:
parts and their libraries:
SparkFun-Connectors: Licensing: Creative Commons ShareAlike 4.0 International - https://creativecommons.org/licenses/by-sa/4.0
